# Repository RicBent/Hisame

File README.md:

# Hisame  
氷雨 - IceStorm

### Development board for the Lattice iCE40 HX1K FPGA

Features:

* 8 LEDs
* 8 Switches
* On board Oscillator
* 128K SRAM
* 44 available IO on header pins

It allows 3 modes of operation:

1. Configuring from SPI flash memory
2. Configuring from an external SPI master device such as a Raspberry Pi (3.3V!)
3. Programming the SPI flash memory from an external SPI master device

Binaries can be built with the IceStorm toolchain or the official Lattice tools.

Bugs:

* GNDPLL is connected to Ground. Using the PLLs might cause issues.
* For FPGA configuration from SPI flash SS and CS_FLASH must be connected.  
  Fix: Don't place R5 and put a jumper between SS1 and SS2 when FPGA should configure from SPI flash.

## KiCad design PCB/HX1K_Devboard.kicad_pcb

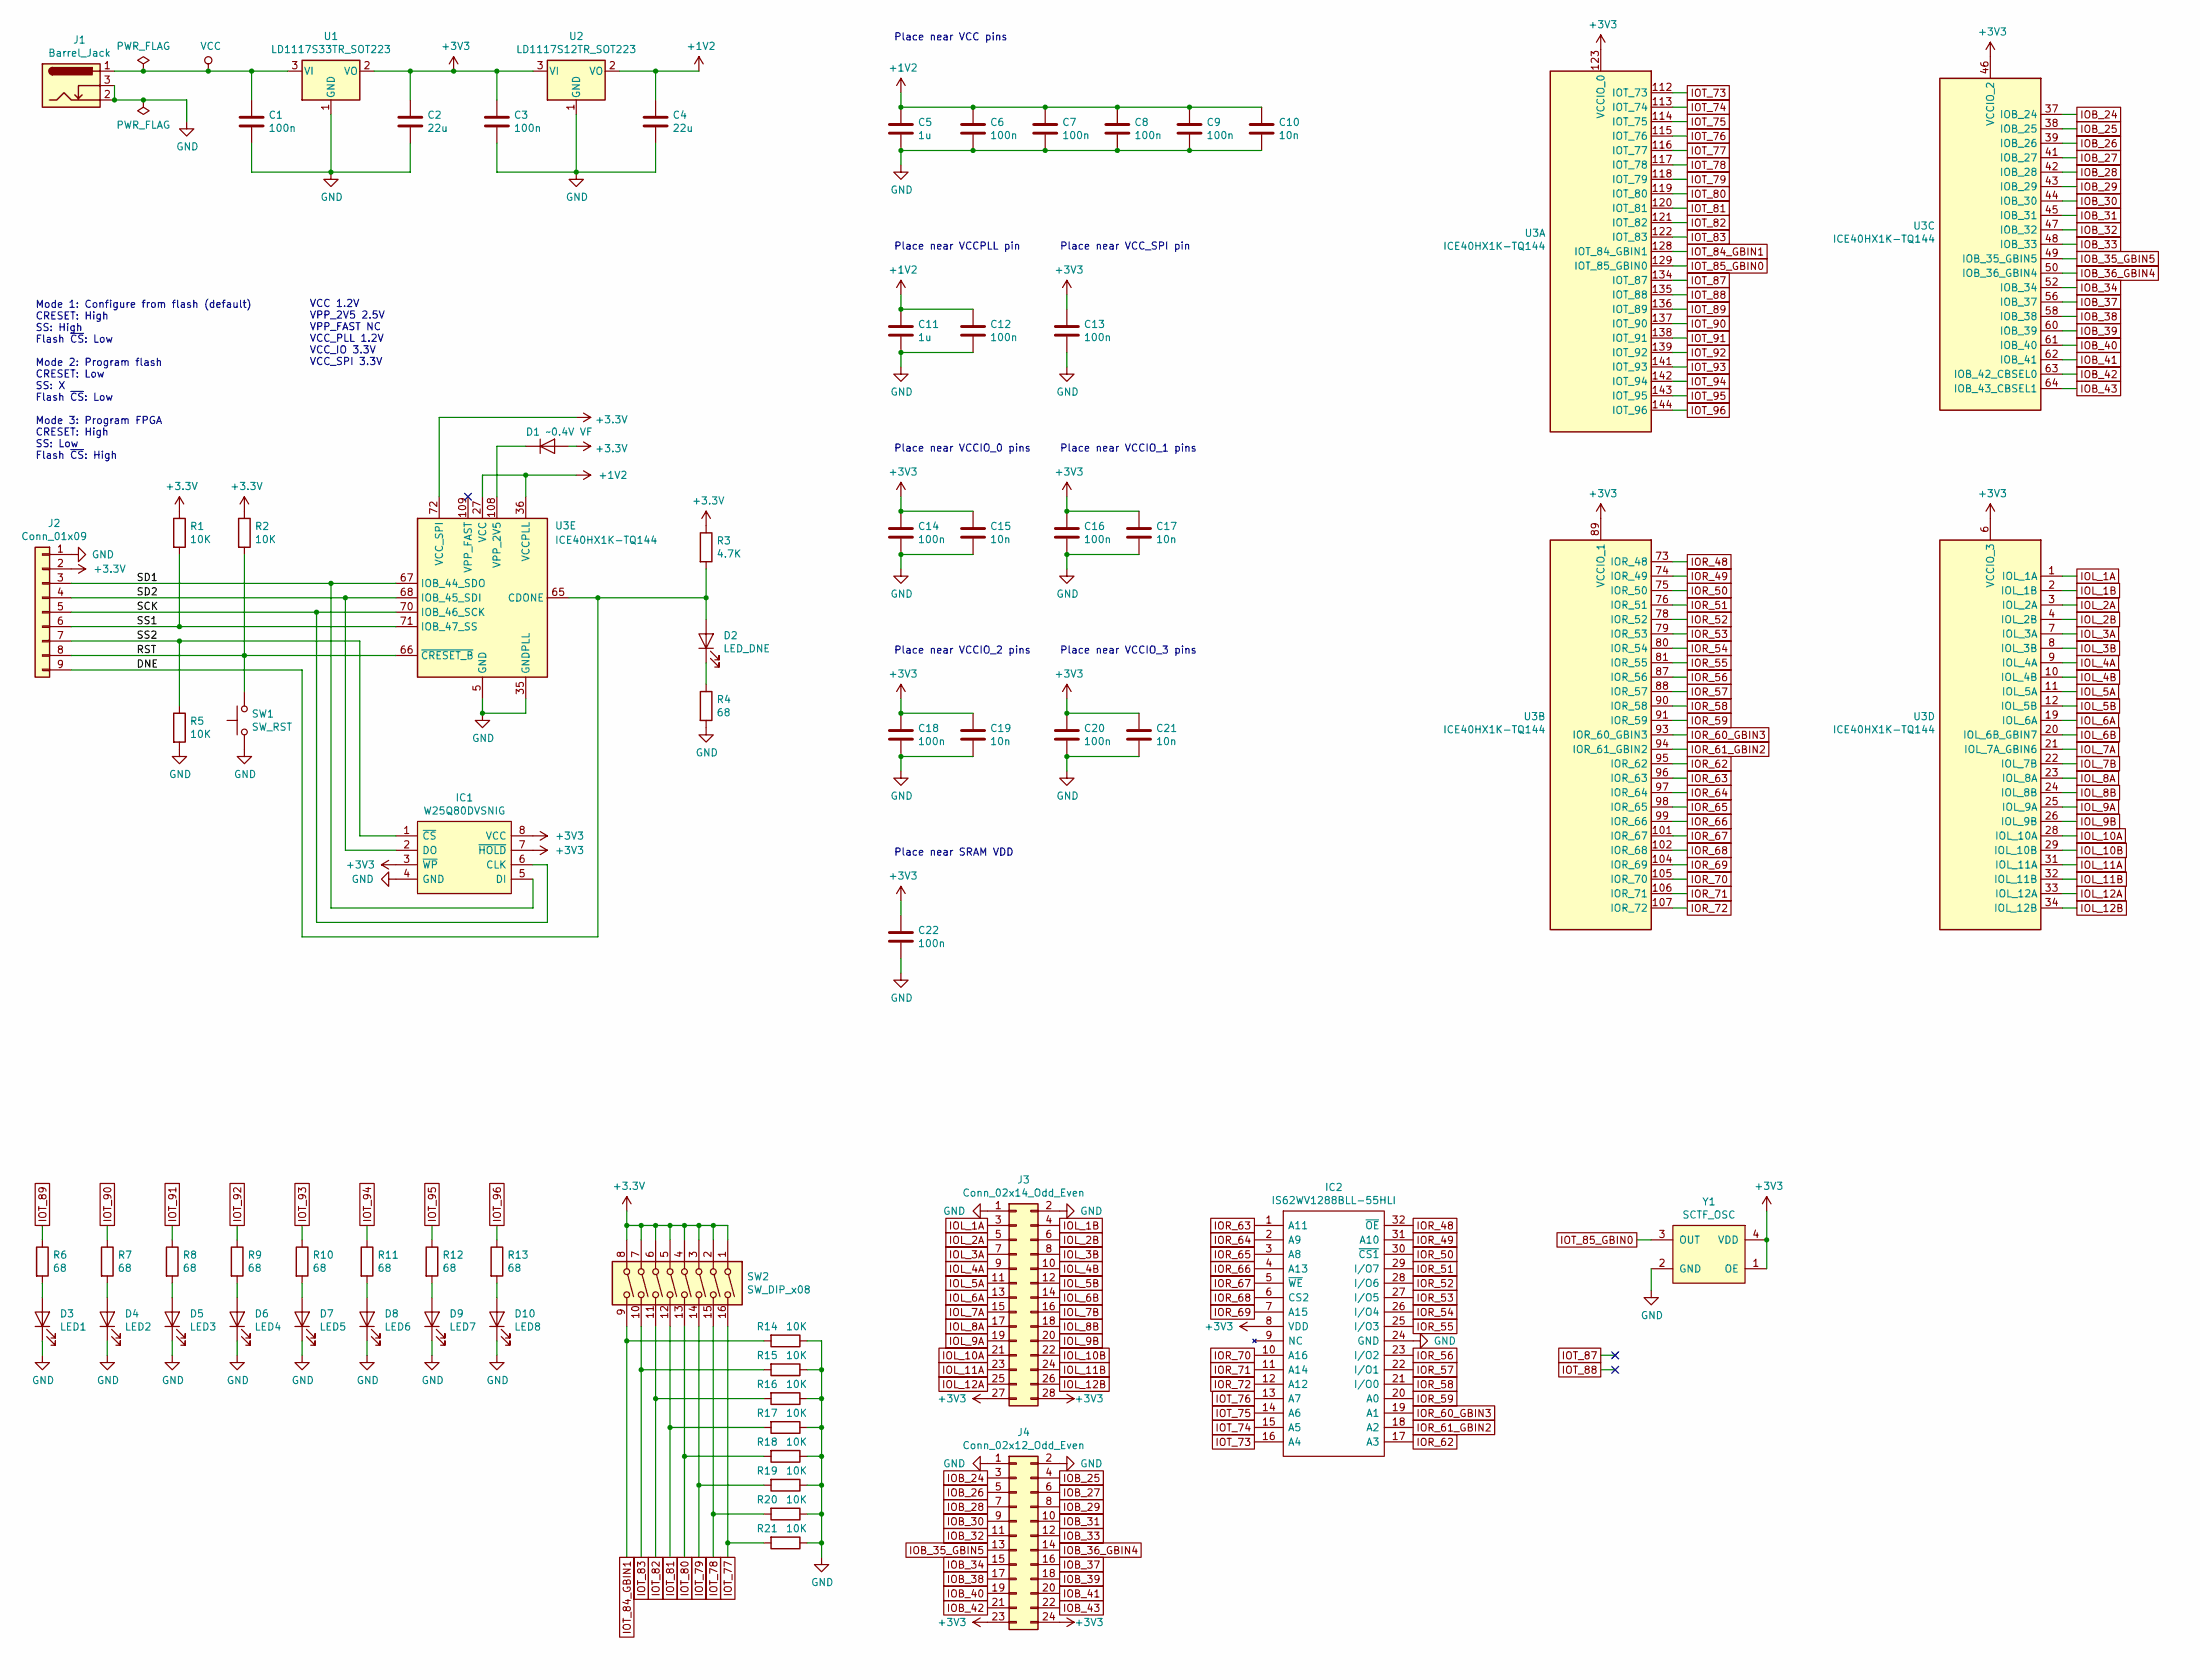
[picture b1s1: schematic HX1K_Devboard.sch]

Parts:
C1, C3, C6, C7, C8, C9, C12, C13, C14, C16, C18, C20, C22: 100n; C_0603_1608Metric_Pad1.05x0.95mm_HandSolder
C2, C4: 22u; CP_EIA-3216-18_Kemet-A_Pad1.58x1.35mm_HandSolder
C5, C11: 1u; C_0603_1608Metric_Pad1.05x0.95mm_HandSolder
C10, C15, C17, C19, C21: 10n; C_0603_1608Metric_Pad1.05x0.95mm_HandSolder
D1: ~~0.4V VF; D_SOD-323
D2: LED_DNE; LED_0603_1608Metric_Pad1.05x0.95mm_HandSolder
D3: LED1; LED_0603_1608Metric_Pad1.05x0.95mm_HandSolder
D4: LED2; LED_0603_1608Metric_Pad1.05x0.95mm_HandSolder
D5: LED3; LED_0603_1608Metric_Pad1.05x0.95mm_HandSolder
D6: LED4; LED_0603_1608Metric_Pad1.05x0.95mm_HandSolder
D7: LED5; LED_0603_1608Metric_Pad1.05x0.95mm_HandSolder
D8: LED6; LED_0603_1608Metric_Pad1.05x0.95mm_HandSolder
D9: LED7; LED_0603_1608Metric_Pad1.05x0.95mm_HandSolder
D10: LED8; LED_0603_1608Metric_Pad1.05x0.95mm_HandSolder
IC1: W25Q80DVSNIG; SOIC127P600X175-8N; Manufacturer_Part_Number W25Q80DVSNIG
IC2: IS62WV1288BLL-55HLI; SOP50P2000X120-32N; Manufacturer_Part_Number IS62WV1288BLL-55HLI; Mouser Part Number 87062WV1288BLL55HLI
J1: Barrel_Jack; BarrelJack_Horizontal
J2: Conn_01x09; PinHeader_1x09_P2.54mm_Vertical
J3: Conn_02x14_Odd_Even; PinHeader_2x14_P2.54mm_Vertical
J4: Conn_02x12_Odd_Even; PinHeader_2x12_P2.54mm_Vertical
R1, R2, R5, R14, R15, R16, R17, R18, R19, R20, R21: 10K; R_0603_1608Metric_Pad1.05x0.95mm_HandSolder
R3: 4.7K; R_0603_1608Metric_Pad1.05x0.95mm_HandSolder
R4, R6, R7, R8, R9, R10, R11, R12, R13: 68; R_0603_1608Metric_Pad1.05x0.95mm_HandSolder
SW1: SW_RST; SW_PUSH_6mm
SW2: SW_DIP_x08; SW_DIP_SPSTx08_Slide_9.78x22.5mm_W7.62mm_P2.54mm
U1: LD1117S33TR_SOT223; SOT-223
U2: LD1117S12TR_SOT223; SOT-223
U3: ICE40HX1K-TQ144; TQFP-144_20x20mm_P0.5mm
Y1: SCTF_OSC; Oscillator_SCTF_5032

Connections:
+1V2: C4.1, C5.1, C6.1, C7.1, C8.1, C9.1, C10.1, C11.1, C12.1, U2.2 (VO), U3.27 (VCC), U3.36 (VCCPLL), U3.51 (VCC), U3.92 (VCC), U3.111 (VCC)
/DNE: D2.2 (A), J2.9, R3.2, U3.65 (CDONE)
/RST: J2.8, R2.2, SW1.2, U3.66 (~CRESET_B)
/SCK: IC1.6 (CLK), J2.5, U3.70 (IOB_46_SCK)
/SD1: IC1.5 (DI), J2.3, U3.67 (IOB_44_SDO)
/SD2: IC1.2 (DO), J2.4, U3.68 (IOB_45_SDI)
/SS1: J2.6, R1.2, U3.71 (IOB_47_SS)
/SS2: IC1.1 (~CS), J2.7, R5.1
GND: C1.2, C2.2, C3.2, C4.2, C5.2, C6.2, C7.2, C8.2, C9.2, C10.2, C11.2, C12.2, C13.2, C14.2, C15.2, C16.2, C17.2, C18.2, C19.2, C20.2, C21.2, C22.2, D3.1 (K), D4.1 (K), D5.1 (K), D6.1 (K), D7.1 (K), D8.1 (K), D9.1 (K), D10.1 (K), IC1.4 (GND), IC2.24 (GND), J1.2, J1.3, J2.1, J3.1, J3.2, J4.1, J4.2, R4.2, R5.2, R14.1, R15.1, R16.1, R17.1, R18.1, R19.1, R20.1, R21.1, SW1.1, U1.1 (GND), U2.1 (GND), U3.5 (GND), U3.13 (GND), U3.14 (GND), U3.35 (GNDPLL), U3.59 (GND), U3.69 (GND), U3.86 (GND), U3.103 (GND), U3.132 (GND), U3.140 (GND), Y1.2 (GND)
IOB_24: J4.3, U3.37 (IOB_24)
IOB_25: J4.4, U3.38 (IOB_25)
IOB_26: J4.5, U3.39 (IOB_26)
IOB_27: J4.6, U3.41 (IOB_27)
IOB_28: J4.7, U3.42 (IOB_28)
IOB_29: J4.8, U3.43 (IOB_29)
IOB_30: J4.9, U3.44 (IOB_30)
IOB_31: J4.10, U3.45 (IOB_31)
IOB_32: J4.11, U3.47 (IOB_32)
IOB_33: J4.12, U3.48 (IOB_33)
IOB_34: J4.15, U3.52 (IOB_34)
IOB_35_GBIN5: J4.13, U3.49 (IOB_35_GBIN5)
IOB_36_GBIN4: J4.14, U3.50 (IOB_36_GBIN4)
IOB_37: J4.16, U3.56 (IOB_37)
IOB_38: J4.17, U3.58 (IOB_38)
IOB_39: J4.18, U3.60 (IOB_39)
IOB_40: J4.19, U3.61 (IOB_40)
IOB_41: J4.20, U3.62 (IOB_41)
IOB_42: J4.21, U3.63 (IOB_42_CBSEL0)
IOB_43: J4.22, U3.64 (IOB_43_CBSEL1)
IOL_1A: J3.3, U3.1 (IOL_1A)
IOL_1B: J3.4, U3.2 (IOL_1B)
IOL_2A: J3.5, U3.3 (IOL_2A)
IOL_2B: J3.6, U3.4 (IOL_2B)
IOL_3A: J3.7, U3.7 (IOL_3A)
IOL_3B: J3.8, U3.8 (IOL_3B)
IOL_4A: J3.9, U3.9 (IOL_4A)
IOL_4B: J3.10, U3.10 (IOL_4B)
IOL_5A: J3.11, U3.11 (IOL_5A)
IOL_5B: J3.12, U3.12 (IOL_5B)
IOL_6A: J3.13, U3.19 (IOL_6A)
IOL_6B: J3.14, U3.20 (IOL_6B_GBIN7)
IOL_7A: J3.15, U3.21 (IOL_7A_GBIN6)
IOL_7B: J3.16, U3.22 (IOL_7B)
IOL_8A: J3.17, U3.23 (IOL_8A)
IOL_8B: J3.18, U3.24 (IOL_8B)
IOL_9A: J3.19, U3.25 (IOL_9A)
IOL_9B: J3.20, U3.26 (IOL_9B)
IOL_10A: J3.21, U3.28 (IOL_10A)
IOL_10B: J3.22, U3.29 (IOL_10B)
IOL_11A: J3.23, U3.31 (IOL_11A)
IOL_11B: J3.24, U3.32 (IOL_11B)
IOL_12A: J3.25, U3.33 (IOL_12A)
IOL_12B: J3.26, U3.34 (IOL_12B)
IOR_48: IC2.32 (~OE), U3.73 (IOR_48)
IOR_49: IC2.31 (A10), U3.74 (IOR_49)
IOR_50: IC2.30 (~CS1), U3.75 (IOR_50)
IOR_51: IC2.29 (I/O7), U3.76 (IOR_51)
IOR_52: IC2.28 (I/O6), U3.78 (IOR_52)
IOR_53: IC2.27 (I/O5), U3.79 (IOR_53)
IOR_54: IC2.26 (I/O4), U3.80 (IOR_54)
IOR_55: IC2.25 (I/O3), U3.81 (IOR_55)
IOR_56: IC2.23 (I/O2), U3.87 (IOR_56)
IOR_57: IC2.22 (I/O1), U3.88 (IOR_57)
IOR_58: IC2.21 (I/O0), U3.90 (IOR_58)
IOR_59: IC2.20 (A0), U3.91 (IOR_59)
IOR_60_GBIN3: IC2.19 (A1), U3.93 (IOR_60_GBIN3)
IOR_61_GBIN2: IC2.18 (A2), U3.94 (IOR_61_GBIN2)
IOR_62: IC2.17 (A3), U3.95 (IOR_62)
IOR_63: IC2.1 (A11), U3.96 (IOR_63)
IOR_64: IC2.2 (A9), U3.97 (IOR_64)
IOR_65: IC2.3 (A8), U3.98 (IOR_65)
IOR_66: IC2.4 (A13), U3.99 (IOR_66)
IOR_67: IC2.5 (~WE), U3.101 (IOR_67)
IOR_68: IC2.6 (CS2), U3.102 (IOR_68)
IOR_69: IC2.7 (A15), U3.104 (IOR_69)
IOR_70: IC2.10 (A16), U3.105 (IOR_70)
IOR_71: IC2.11 (A14), U3.106 (IOR_71)
IOR_72: IC2.12 (A12), U3.107 (IOR_72)
IOT_73: IC2.16 (A4), U3.112 (IOT_73)
IOT_74: IC2.15 (A5), U3.113 (IOT_74)
IOT_75: IC2.14 (A6), U3.114 (IOT_75)
IOT_76: IC2.13 (A7), U3.115 (IOT_76)
IOT_77: R21.2, SW2.16, U3.116 (IOT_77)
IOT_78: R20.2, SW2.15, U3.117 (IOT_78)
IOT_79: R19.2, SW2.14, U3.118 (IOT_79)
IOT_80: R18.2, SW2.13, U3.119 (IOT_80)
IOT_81: R17.2, SW2.12, U3.120 (IOT_81)
IOT_82: R16.2, SW2.11, U3.121 (IOT_82)
IOT_83: R15.2, SW2.10, U3.122 (IOT_83)
IOT_84_GBIN1: R14.2, SW2.9, U3.128 (IOT_84_GBIN1)
IOT_85_GBIN0: U3.129 (IOT_85_GBIN0), Y1.3 (OUT)
IOT_87: U3.134 (IOT_87)
IOT_88: U3.135 (IOT_88)
IOT_89: R6.1, U3.136 (IOT_89)
IOT_90: R7.1, U3.137 (IOT_90)
IOT_91: R8.1, U3.138 (IOT_91)
IOT_92: R9.1, U3.139 (IOT_92)
IOT_93: R10.1, U3.141 (IOT_93)
IOT_94: R11.1, U3.142 (IOT_94)
IOT_95: R12.1, U3.143 (IOT_95)
IOT_96: R13.1, U3.144 (IOT_96)
unnamed: D1.1 (K), U3.108 (VPP_2V5)
unnamed: D2.1 (K), R4.1
unnamed: D3.2 (A), R6.2
unnamed: D4.2 (A), R7.2
unnamed: D5.2 (A), R8.2
unnamed: D6.2 (A), R9.2
unnamed: D7.2 (A), R10.2
unnamed: D8.2 (A), R11.2
unnamed: D9.2 (A), R12.2
unnamed: D10.2 (A), R13.2
VCC: C1.1, J1.1, U1.3 (VI)

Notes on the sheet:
VCC 1.2V VPP_2V5 2.5V VPP_FAST NC VCC_PLL 1.2V VCC_IO 3.3V VCC_SPI 3.3V
Mode 1: Configure from flash (default) CRESET: High SS: High Flash ~CS~: Low Mode 2: Program flash CRESET: Low SS: X Flash ~CS~: Low Mode 3: Program FPGA CRESET: High SS: Low Flash ~CS~: High
Place near VCC pins
Place near VCCPLL pin
Place near VCC_SPI pin
Place near VCCIO_0 pins
Place near VCCIO_1 pins
Place near VCCIO_2 pins
Place near VCCIO_3 pins
Place near SRAM VDD

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
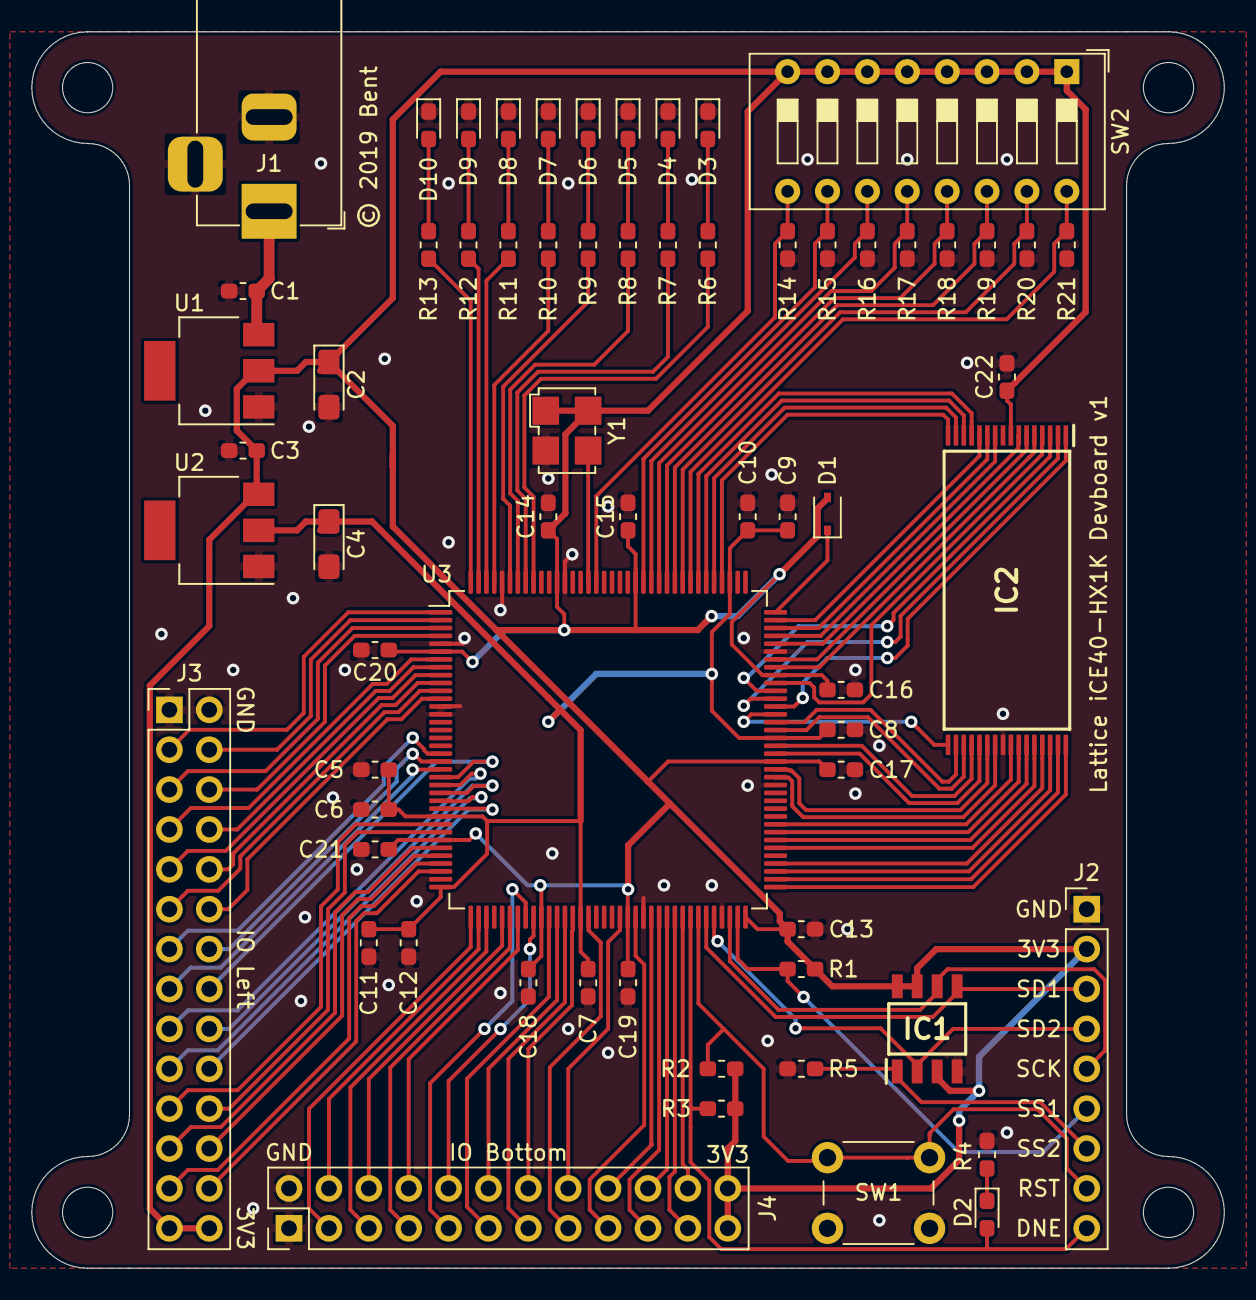
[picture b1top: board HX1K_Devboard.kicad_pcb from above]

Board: 2 copper layers, 75.9 x 78.7 mm, 65 parts (0 on the bottom side), 111 nets.

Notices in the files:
PCB/HX1K_Devboard.kicad_pcb:
© 2019 Bent
